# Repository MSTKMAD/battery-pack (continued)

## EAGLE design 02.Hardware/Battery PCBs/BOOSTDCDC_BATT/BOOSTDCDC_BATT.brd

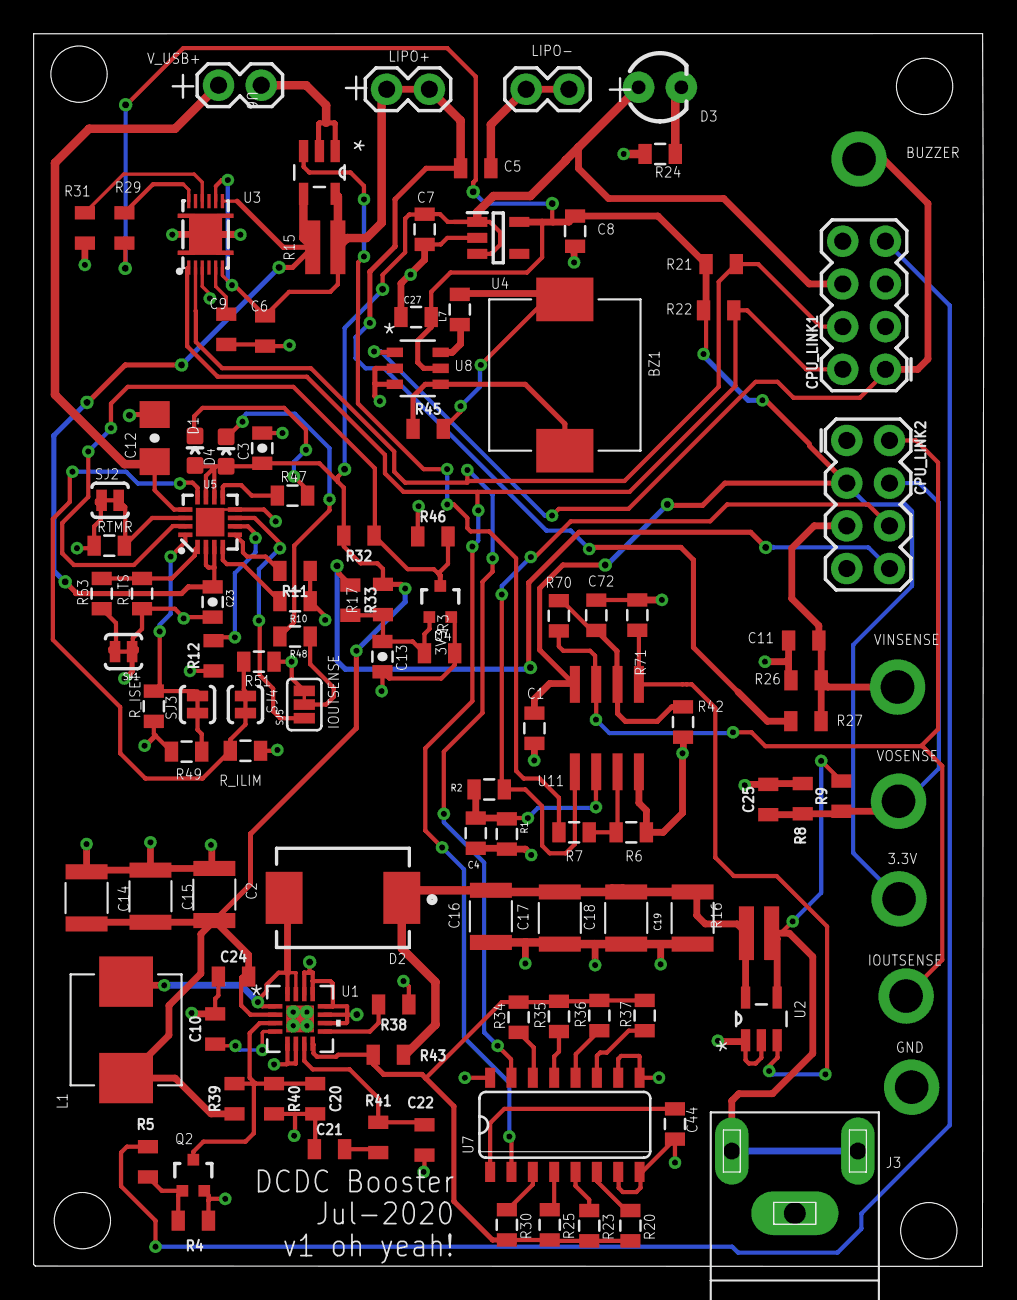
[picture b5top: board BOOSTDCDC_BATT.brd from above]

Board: 2 copper layers, 56.5 x 73.3 mm, 114 parts (0 on the bottom side), 63 nets.

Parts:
3V3: M01PTH_2MM; 1X01_2MM
BUZZER: M01PTH_2MM; 1X01_2MM
BZ1: PKMCS0909E4000-R1; PKMCS0909
C1, C27, C44: 100n; 0805
C2, C14, C15, C16, C17, C18, C19: 47uF 25V; WCAP-CSGP_1210
C3, C13, C23: 10uF; 0805-CAP
C4, C72: N.C.; 0805
C5, C11, C25: 100n; 0805@1
C6: 1uF / 16V; 0805@1
C7, C8: 4.7uF; 0805
C9: 470n; 0805@1
C10, C20: 47n 35V; 0805@1
C12: 1.0uF; 1206-CAP
C21, C24: 100n 50V; 0805@1
C22: 270p 50V; 0805@1
CPU_LINK1, CPU_LINK2: 2X4
D1: BLUE; LED-0603
D2: B520C-13-F; DIOM7959X250N
D3: LED_3MM
D4: RED; LED-0603
GND: M01PTH_2MM; 1X01_2MM
IOUTSENSE: M01PTH_2MM; 1X01_2MM
J3: PJRAN1X1U01X
L1: 2.2uH - 74437346022; INDM7366X500
L7: MMZ2012Y202BT000; 0805
LIPO+: LiPoIN; 1X02
LIPO-: LiPoIN; 1X02
Q2, Q4: 2N7002PW; SOT323
R1, R2, R29, R31, R46, R53, R70: 10k; 0805
R3, R11, R12: 1M; 0805
R4, R32: 470k; 0805
R5, R33: 33R; 0805
R6: 82k; 0805
R7: 330k; 0805
R8, R27: 39k; 0805
R9: 150k; 0805
R10, R47: 180; 0805
R15, R16: 0.01R; WRIS-KWKH_0612
R17, R45: 330R; 0805
R20: 11K; 0805
R21, R22: 4k7; 0805
R23: 5K6; 0805
R24: 200R; 0805
R25: 2K8; 0805
R26: 75k; 0805
R30: 1K4; 0805
R34: 180K; 0805
R35: 91K; 0805
R36: 43K; 0805
R37: 22K; 0805
R38, R39, R40, R43: 78.7k; 0805
R41: 1.87k; 0805
R42: 3k3; 0805
R48: 1k; 0805
R49: 590; 0805
R51: 1.1k; 0805
R71: 100k; 0805
RTMR: 0805
R_ILIM: 0805
R_ISET: 0805
R_TS: 0805
SJ1, SJ2, SJ3, SJ4: PAD-JUMPER-2-NC_BY_TRACE_YES_SILK
SJ5: PAD-JUMPER-3-2OF3_NC_BY_TRACE_YES_SILK_FULL_BOX
U1: TPS55330RTET; RTE16_1P66X1P66_TEX
U2, U6: MAX9938TEUK+T (G=25); SOT95P280X145-5N
U3: BQ27441-G1; PDSO-N12
U4: AP2205-W5-33Y; SOT95P282X145-5N
U5: BQ24075; PVQFN-N16
U7: TPIC2810D; SO16
U8: SN74LVC1G19DBVR; DBV6
U11: MCP6L02SN; SO08
VINSENSE: M01PTH_2MM; 1X01_2MM
VOSENSE: M01PTH_2MM; 1X01_2MM
V_USB+: 1X02

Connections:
1.8V: C9.1, U3.5
3.3V: 3V3.1, C1.1, C8.1, C27.2, CPU_LINK2.3, R21.1, R22.1, R29.2, U4.5, U8.5, U11.8
!CE!: R10.2, U5.4
!CHG!: R47.1, U5.9
!PGOOD!: SJ5.1, U5.7
#EN_DCDC: CPU_LINK1.7, R5.2
#SHIPPINGMOD: CPU_LINK2.8, R33.1
BATTERY_IN: C5.1, C6.1, LIPO+.1, LIPO+.2, R15.2, R27.2, U3.6, U3.8, U6.5
BUZZER: BUZZER.1, CPU_LINK1.1, U8.1
EN1: R12.2, U5.6
EN2: R11.2, U5.5
GND: C1.2, C2.1, C3.2, C4.1, C5.2, C6.2, C7.2, C8.2, C9.2, C10.2, C11.2, C12.2, C13.2, C14.1, C15.1, C16.1, C17.1, C18.1, C19.1, C20.2, C21.1, C22.1, C23.2, C24.1, C25.2, C27.1, C44.1, C72.1, CPU_LINK1.8, CPU_LINK2.1, GND.1, J3.1, LIPO-.1, LIPO-.2, Q2.2, Q4.2, R1.2, R3.1, R4.1, R6.2, R8.1, R10.1, R11.1, R12.1, R24.1, R26.1, R31.1, R38.1, R40.2, R42.1, R46.1, R49.1, R51.1, R71.1, RTMR.1, R_ILIM.1, R_ISET.1, R_TS.1, SJ1.1, SJ2.1, SJ5.3, U1.5, U1.6, U1.10, U1.11, U1.12, U1.13, U1.14, U1.17, U2.1, U2.2, U3.3, U3.EP, U3.EP1, U3.EP2, U3.EP3, U3.EP4, U4.2, U5.8, U5.EP, U6.1, U6.2, U7.7, U7.8, U7.9, U7.10, U7.16, U8.2, U8.3, U11.4, V_USB+.2
GPOUT: R29.1, U3.12
IBATTSENSE: CPU_LINK2.6, R2.2, U11.1
ILIM: R_ILIM.2, SJ4.2, U5.12
IOUTSENSE: CPU_LINK2.2, IOUTSENSE.1, R70.2, U11.7
ISET: R_ISET.2, SJ3.2, U5.16
unnamed: D4.C, R48.2
unnamed: Q2.1, R4.2, R5.1
unnamed: D1.C, R47.2
unnamed: R53.1, SJ1.2
unnamed: R71.2, U2.3, U11.5
unnamed: R51.2, SJ4.1
unnamed: C4.2, R1.1, R2.1, U11.2
unnamed: R6.1, R7.2, U11.3
unnamed: J3.2, J3.3, R9.2, R16.1, U2.4
unnamed: R49.2, SJ3.1
unnamed: R48.1, SJ5.2
unnamed: R20.1, U7.6
unnamed: L7.1, U8.6
unnamed: D3.K, R24.2
unnamed: BZ1.1, L7.2, R45.2
unnamed: R23.1, U7.5
unnamed: BZ1.2, R45.1, U8.4
unnamed: C13.1, Q4.1, R3.2, R17.1, R33.2
unnamed: R25.1, U7.4
unnamed: R30.1, U7.3
unnamed: R34.1, U7.14
unnamed: R35.1, U7.13
unnamed: R36.1, U7.12
unnamed: R37.1, U7.11
unnamed: C10.1, U1.4
unnamed: D2.A, L1.2, U1.1, U1.15, U1.16
unnamed: R38.2, U1.9
unnamed: C20.1, Q2.3, R39.2, R40.1, U1.3
unnamed: C21.2, R41.2
unnamed: C22.2, R41.1, U1.7
unnamed: R20.2, R23.2, R25.2, R30.2, R34.2, R35.2, R36.2, R37.2, R43.2, U1.8
unnamed: R7.1, U6.3
unnamed: C72.2, R42.2, R70.1, U11.6
SCL: CPU_LINK1.4, R21.2, U3.2, U7.15
SDA: CPU_LINK1.2, R22.2, U3.1, U7.2
SYSOFF: Q4.3, R32.1, R46.2, U5.15
TMR: RTMR.2, SJ2.2, U5.14
TS: R31.2, U3.10
TS1: R53.2, R_TS.2, U5.1
VBATT: C23.1, R15.1, U3.7, U5.2, U5.3, U6.4
VCC-ISO: C44.2, U7.1
VINSENSE: C11.1, CPU_LINK2.5, R26.2, R27.1, VINSENSE.1
VOSENSE: C25.1, CPU_LINK2.4, R8.2, R9.1, VOSENSE.1
VSOURCE: C16.2, C17.2, C18.2, C19.2, D2.C, R16.2, R43.1, U2.5
VSYS: C2.2, C3.1, C7.1, C14.2, C15.2, C24.2, CPU_LINK1.6, D1.A, D3.A, D4.A, L1.1, R17.2, R32.2, R39.1, U1.2, U4.1, U4.3, U5.10, U5.11
V_USB: C12.1, U5.13, V_USB+.1
